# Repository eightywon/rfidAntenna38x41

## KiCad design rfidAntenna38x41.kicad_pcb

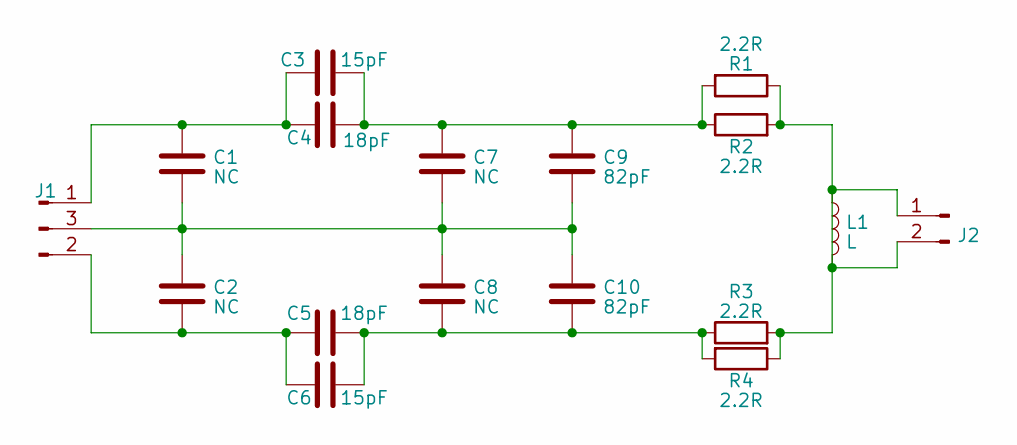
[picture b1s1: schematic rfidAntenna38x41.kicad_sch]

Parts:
C1, C2, C7, C8: NC; C_0805_2012Metric
C3, C6: 15pF; C_0805_2012Metric
C4, C5: 18pF; C_0805_2012Metric; LCSC C113825
C9, C10: 82pF; C_0805_2012Metric
J1: Conn_01x03_Pin; PinHeader_1x03_P2.54mm_Vertical
J2: Conn_01x02_Pin; PinHeader_1x02_P2.54mm_Vertical
L1: L; rfidAntenna38x41
R1, R2, R3, R4: 2.2R; R_0805_2012Metric

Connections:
unnamed: C3.2, C4.2, C7.1, C9.1, R1.2, R2.1
unnamed: C5.2, C6.1, C8.2, C10.2, R3.1, R4.2
unnamed: C1.1, C3.1, C4.1, J1.1
unnamed: C1.2, C2.1, C7.2, C8.1, C9.2, C10.1, J1.3 (Pin_2)
unnamed: C2.2, C5.1, C6.2, J1.2 (Pin_3)
unnamed: J2.1, J2.2, L1.1, L1.2, R1.1, R2.2, R3.2, R4.1

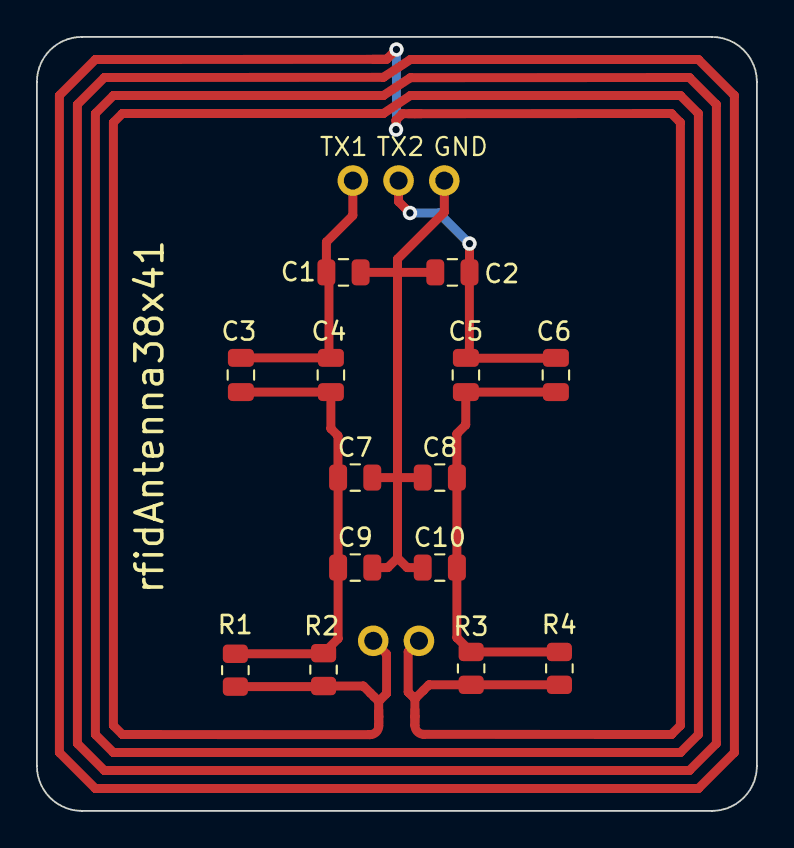
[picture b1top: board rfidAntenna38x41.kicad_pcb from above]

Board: 2 copper layers, 40.0 x 43.0 mm, 17 parts (0 on the bottom side), 6 nets.

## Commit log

2023-09-01 first
